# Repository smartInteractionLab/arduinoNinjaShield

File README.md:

:::::::::::::::::::::::::::::::::::::::::::::::::::::::::::::::
::                                                           ::
::  Smart Design RF Shield (v0.1 and v0.2)                   ::
::                                                           ::
:::::::::::::::::::::::::::::::::::::::::::::::::::::::::::::::

The actual RF omponents on the shield come from Seeed Studio, 
look for their "433Mhz RF link kit" or "433Mhz RF link kit", 
depending on at which frequency you want to use, at

http://www.seeedstudio.com

The shield might be compatible with other similar modules, 
however this has not been tested and should only be done at
your own volition.

You also might want to order stackable headers for the shield
if you're planning on adding another shield, or want to 
connect anything else to the Arduino pins. Such headers can 
be found at most places which deal with Arduino related
hardware, such as Sparkfun, Adafruit.

http://www.sparkfun.com
http://www.adafruit.com

To get the shield to work when it has been populated with the
right components and hooked into the Arduino you need to run 
the RC-Switch library in your Arduino sketch as well. Follow 
the documentation in the library to get your shield running 
in the way you want it to. The library can be found here: 

http://code.google.com/p/rc-switch/

If you do add another shield take into consideration that
digital pins 2 and 7 are used by the RF Shield and thus
cannot be used for other shields. Though, if you only need
TX or RX capability you can free up the according pin. TX 
uses pin 7 and RX uses pin 2.

In case you are planning to use the Arduino as a sensor or 
actuator together with the Ninja Blocks platform there is a 
great tutorial available at http://www.ninjablocks.com called 
"Adding RF 433MHz to your Arduino"

You can read about the process of creating this shield at 

http://www.smartinteractionlab.com

Thank you, and have fun!

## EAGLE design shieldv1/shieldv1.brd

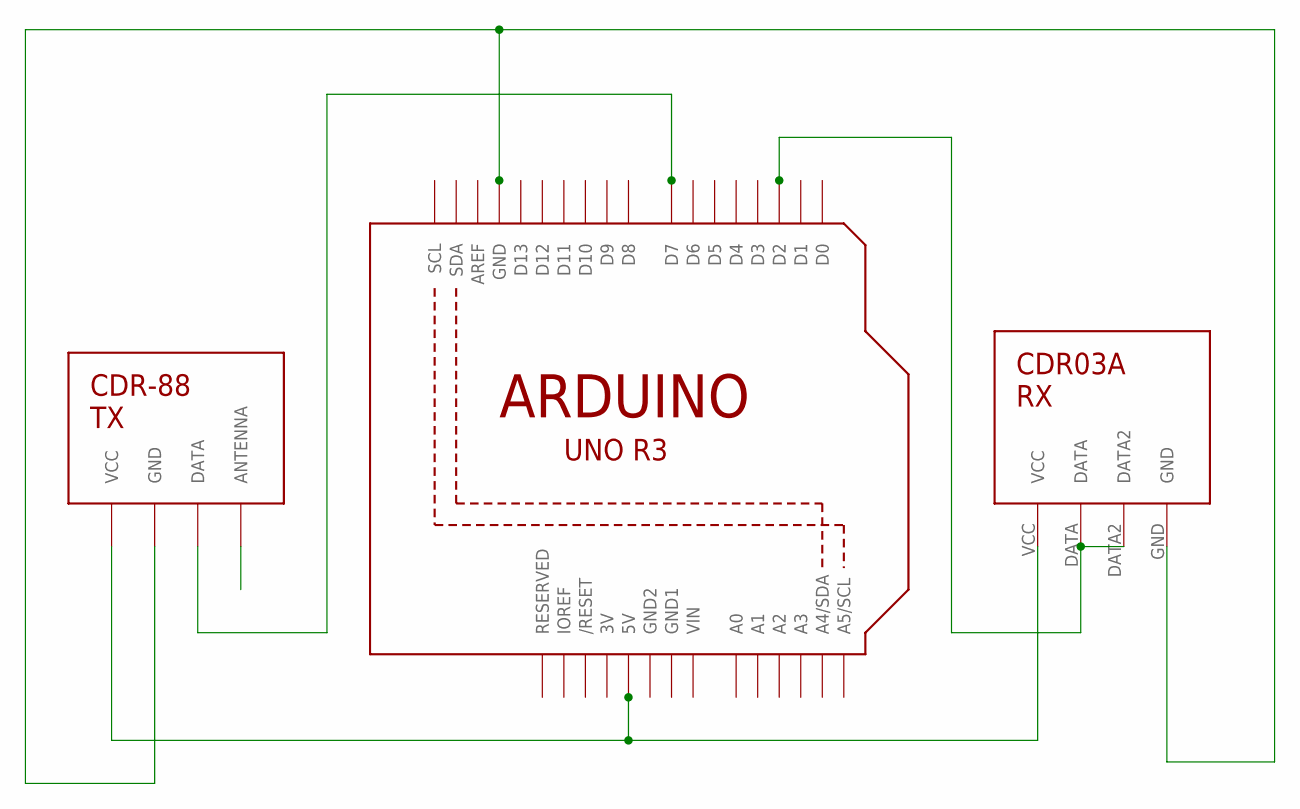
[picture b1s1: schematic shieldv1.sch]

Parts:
U2: ARDUINOR3-DIMENSION; ARDUINOR3
U$1: CDT-88
U$2: CDR03A

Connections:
3V: U2.3V
GND1: U2.GND1
GND2: U2.GND2
unnamed: U2.D7, U$1.DATA
unnamed: U2.D2, U$2.DATA, U$2.DATA2
unnamed: U2.5V, U$1.VCC, U$2.VCC
unnamed: U2.GND, U$1.GND, U$2.GND
VIN: U2.VIN

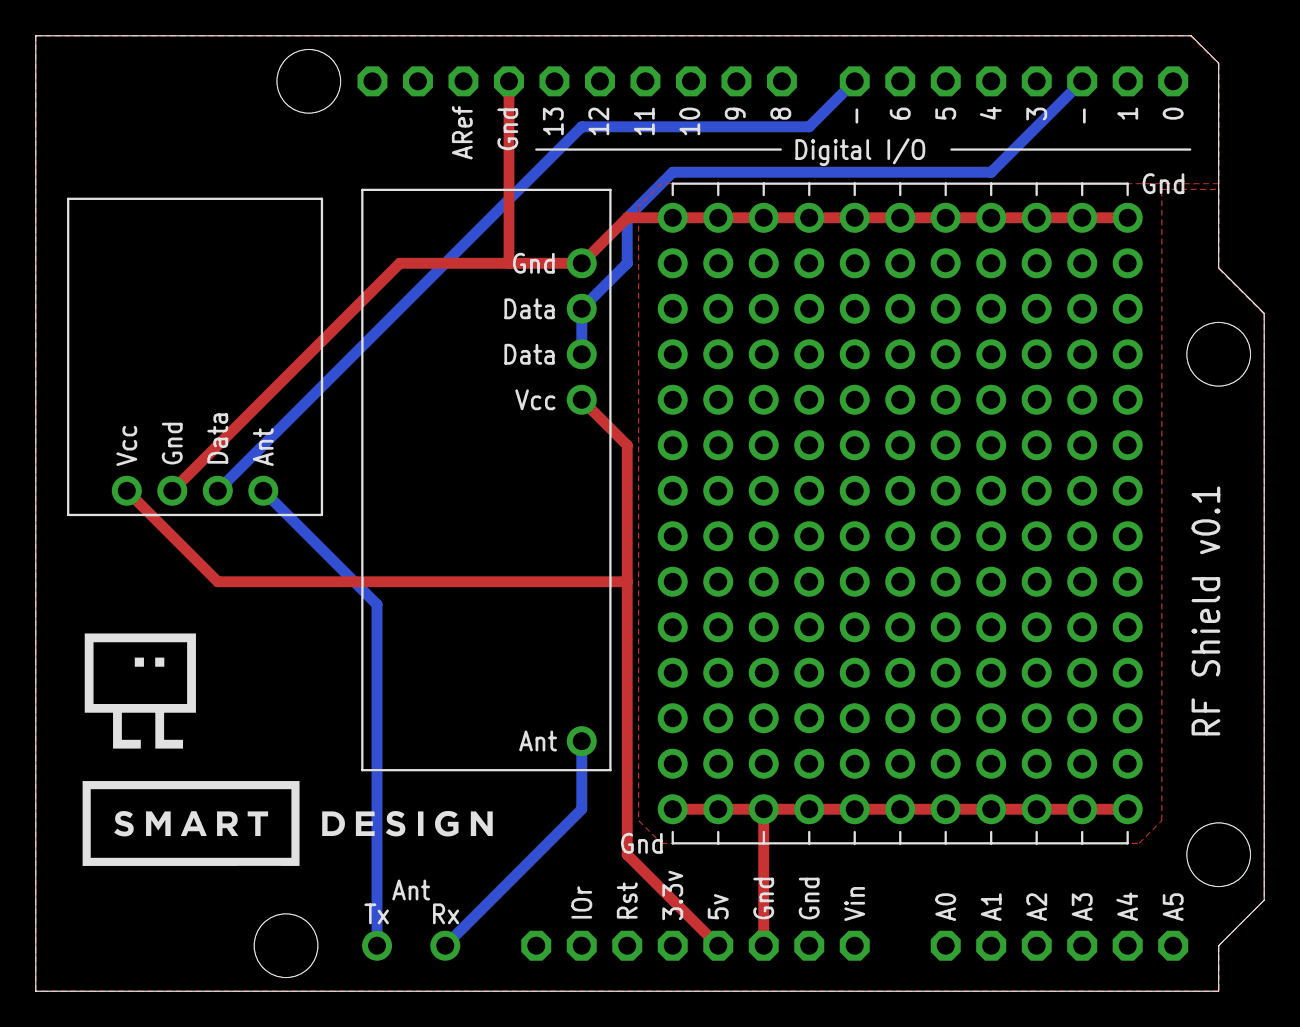
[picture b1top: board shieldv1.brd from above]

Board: 2 copper layers, 68.6 x 53.3 mm, 3 parts (0 on the bottom side), 4 nets.

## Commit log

2013-08-08 Gitignore Added
2013-08-08 Added board schematic
    EAGLE files
2013-12-20 Update README.md
    Changed url for seed studio to seeed.
